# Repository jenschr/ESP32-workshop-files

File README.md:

# ESP32-workshop-files
Kicad files from my two-day workshop at [Bitraf](https://github.com/bitraf) on creating an ESP32 based IoT device from scratch. In the Workshop, attendees will be making an IoT device from scratch using the Open Source EDA software Kicad. [Slides from the workshop](https://www.slideshare.net/jensa/two-day-electronics-workshop-with-kicad-training) can be found at my Slideshare account.

## Reference designs
In the workshop, we'll create our own boards from scratch, but we found that it's convenient to have a project to compare and check things against. In the workshop, the attendees can choose to use either the ESP32 S2/S3 Mini or the ESP32 Wroom 32E modules. The latter requires the use of a serial chip such as the CP2102/04 and this tested design has the required auto-program circuitry.

## Alternate parts
Having a devboard is fun, but having some builtin input and output is even better, so for the attendees that don't have a plan, I've suggested to add an APA102 Dotstar pixel as well as a simple NTC-based temperature sensor. The circuit for these two are in the files for the S2/S3 Mini.

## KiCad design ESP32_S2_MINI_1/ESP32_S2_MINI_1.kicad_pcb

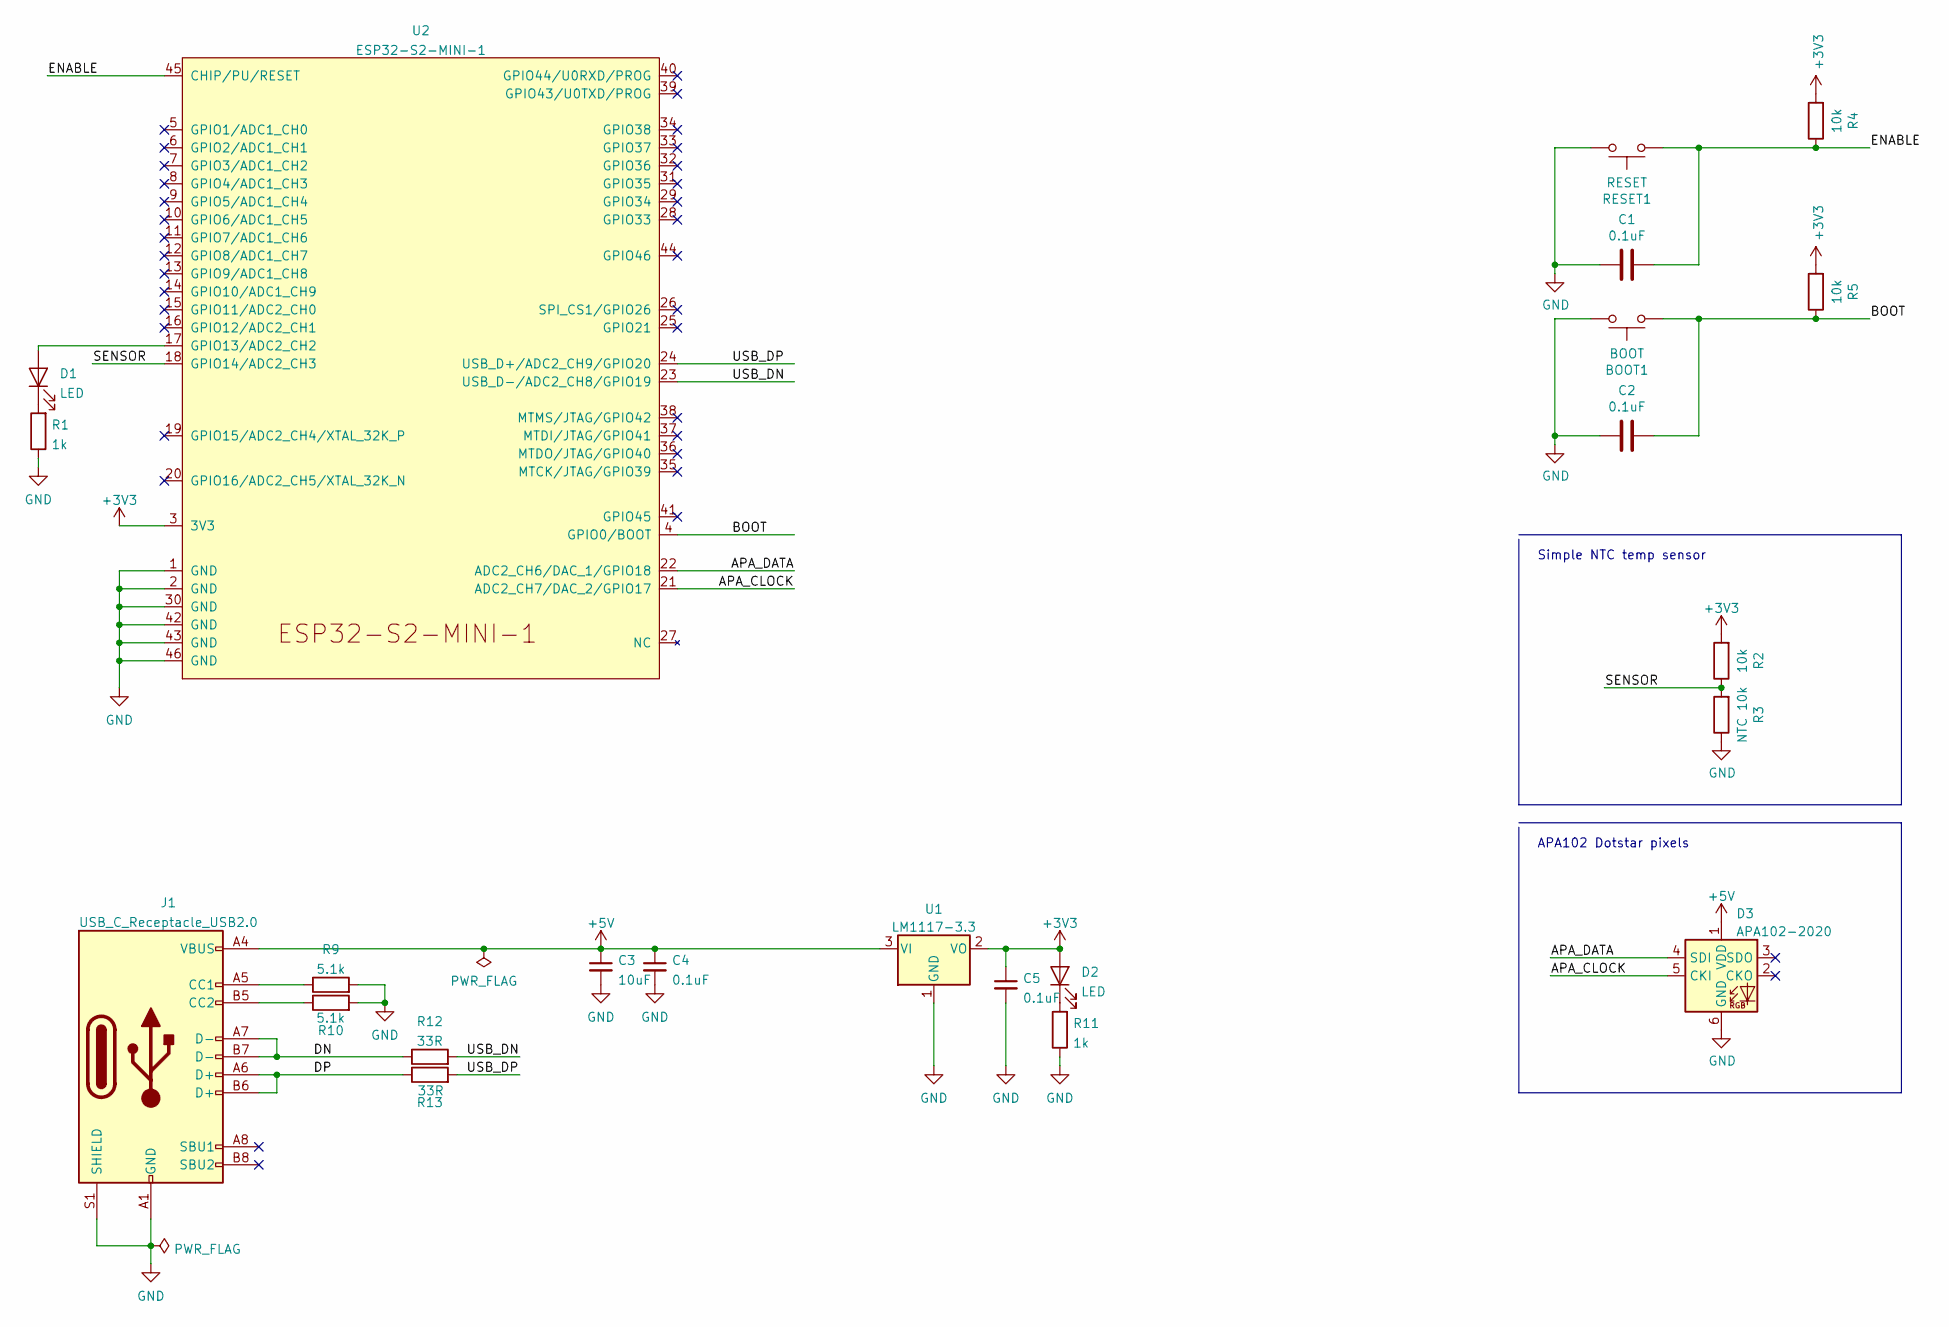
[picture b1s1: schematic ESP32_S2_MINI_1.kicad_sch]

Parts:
BOOT1: BOOT; SW_Push_1P1T_NO_CK_KMR2; MPN KMR241GLFS
C1, C2: 0.1uF; C_0402_1005Metric; MPN CL10B104KO8NFNC
C3: 10uF; C_0603_1608Metric
C4, C5: 0.1uF; C_0402_1005Metric
D1, D2: LED; LED_0402_1005Metric
D3: APA102-2020; LED-APA102-2020
J1: USB_C_Receptacle_USB2.0; TYPE-C-31-M-14
R1, R11: 1k; R_0402_1005Metric
R2, R4, R5: 10k; R_0402_1005Metric; MPN RMCF0603JG10K0
R3: NTC 10k; R_0402_1005Metric; MPN RMCF0603JG10K0
R9, R10: 5.1k; R_0402_1005Metric
R12, R13: 33R; R_0402_1005Metric
RESET1: RESET; SW_Push_1P1T_NO_CK_KMR2; MPN KMR241GLFS
U1: LM1117-3.3; SOT-223
U2: ESP32-S2-MINI-1

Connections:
+3V3: C5.1, D2.2 (A), R2.2, R4.2, R5.2, U1.2 (VO), U2.3 (3V3)
+5V: C3.1, C4.1, D3.1 (VDD), J1.A4 (VBUS), J1.A9 (VBUS), J1.B4 (VBUS), J1.B9 (VBUS), U1.3 (VI)
/APA_CLOCK: D3.5 (CKI), U2.21 (ADC2_CH7/DAC_2/GPIO17)
/APA_DATA: D3.4 (SDI), U2.22 (ADC2_CH6/DAC_1/GPIO18)
/BOOT: BOOT1.1, C2.1, R5.1, U2.4 (GPIO0/BOOT)
/DN: J1.A7 (D-), J1.B7 (D-), R12.1
/DP: J1.A6 (D+), J1.B6 (D+), R13.1
/ENABLE: C1.1, R4.1, RESET1.1, U2.45 (CHIP/PU/RESET)
/SENSOR: R2.1, R3.2, U2.18 (GPIO14/ADC2_CH3)
/USB_DN: R12.2, U2.23 (USB_D-/ADC2_CH8/GPIO19)
/USB_DP: R13.2, U2.24 (USB_D+/ADC2_CH9/GPIO20)
GND: BOOT1.2, C1.2, C2.2, C3.2, C4.2, C5.2, D3.6 (GND), J1.A1 (GND), J1.A12 (GND), J1.B1 (GND), J1.B12 (GND), J1.S1 (SHIELD), R1.1, R3.1, R9.2, R10.2, R11.1, RESET1.2, U1.1 (GND), U2.1 (GND), U2.2 (GND), U2.30 (GND), U2.42 (GND), U2.43 (GND), U2.46 (GND)
unnamed: D1.1 (K), R1.2
unnamed: D1.2 (A), U2.17 (GPIO13/ADC2_CH2)
unnamed: D2.1 (K), R11.2
unnamed: J1.A5 (CC1), R9.1
unnamed: J1.B5 (CC2), R10.1

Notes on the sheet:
Simple NTC temp sensor
APA102 Dotstar pixels

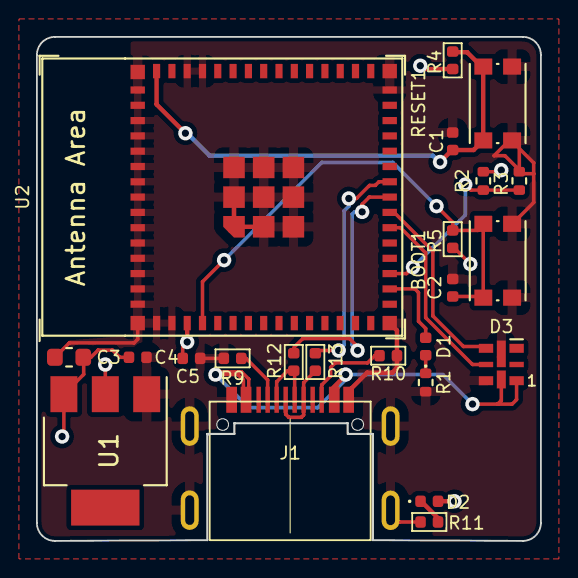
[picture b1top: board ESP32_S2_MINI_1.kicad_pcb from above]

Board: 2 copper layers, 28.0 x 28.0 mm, 23 parts (0 on the bottom side), 17 nets.

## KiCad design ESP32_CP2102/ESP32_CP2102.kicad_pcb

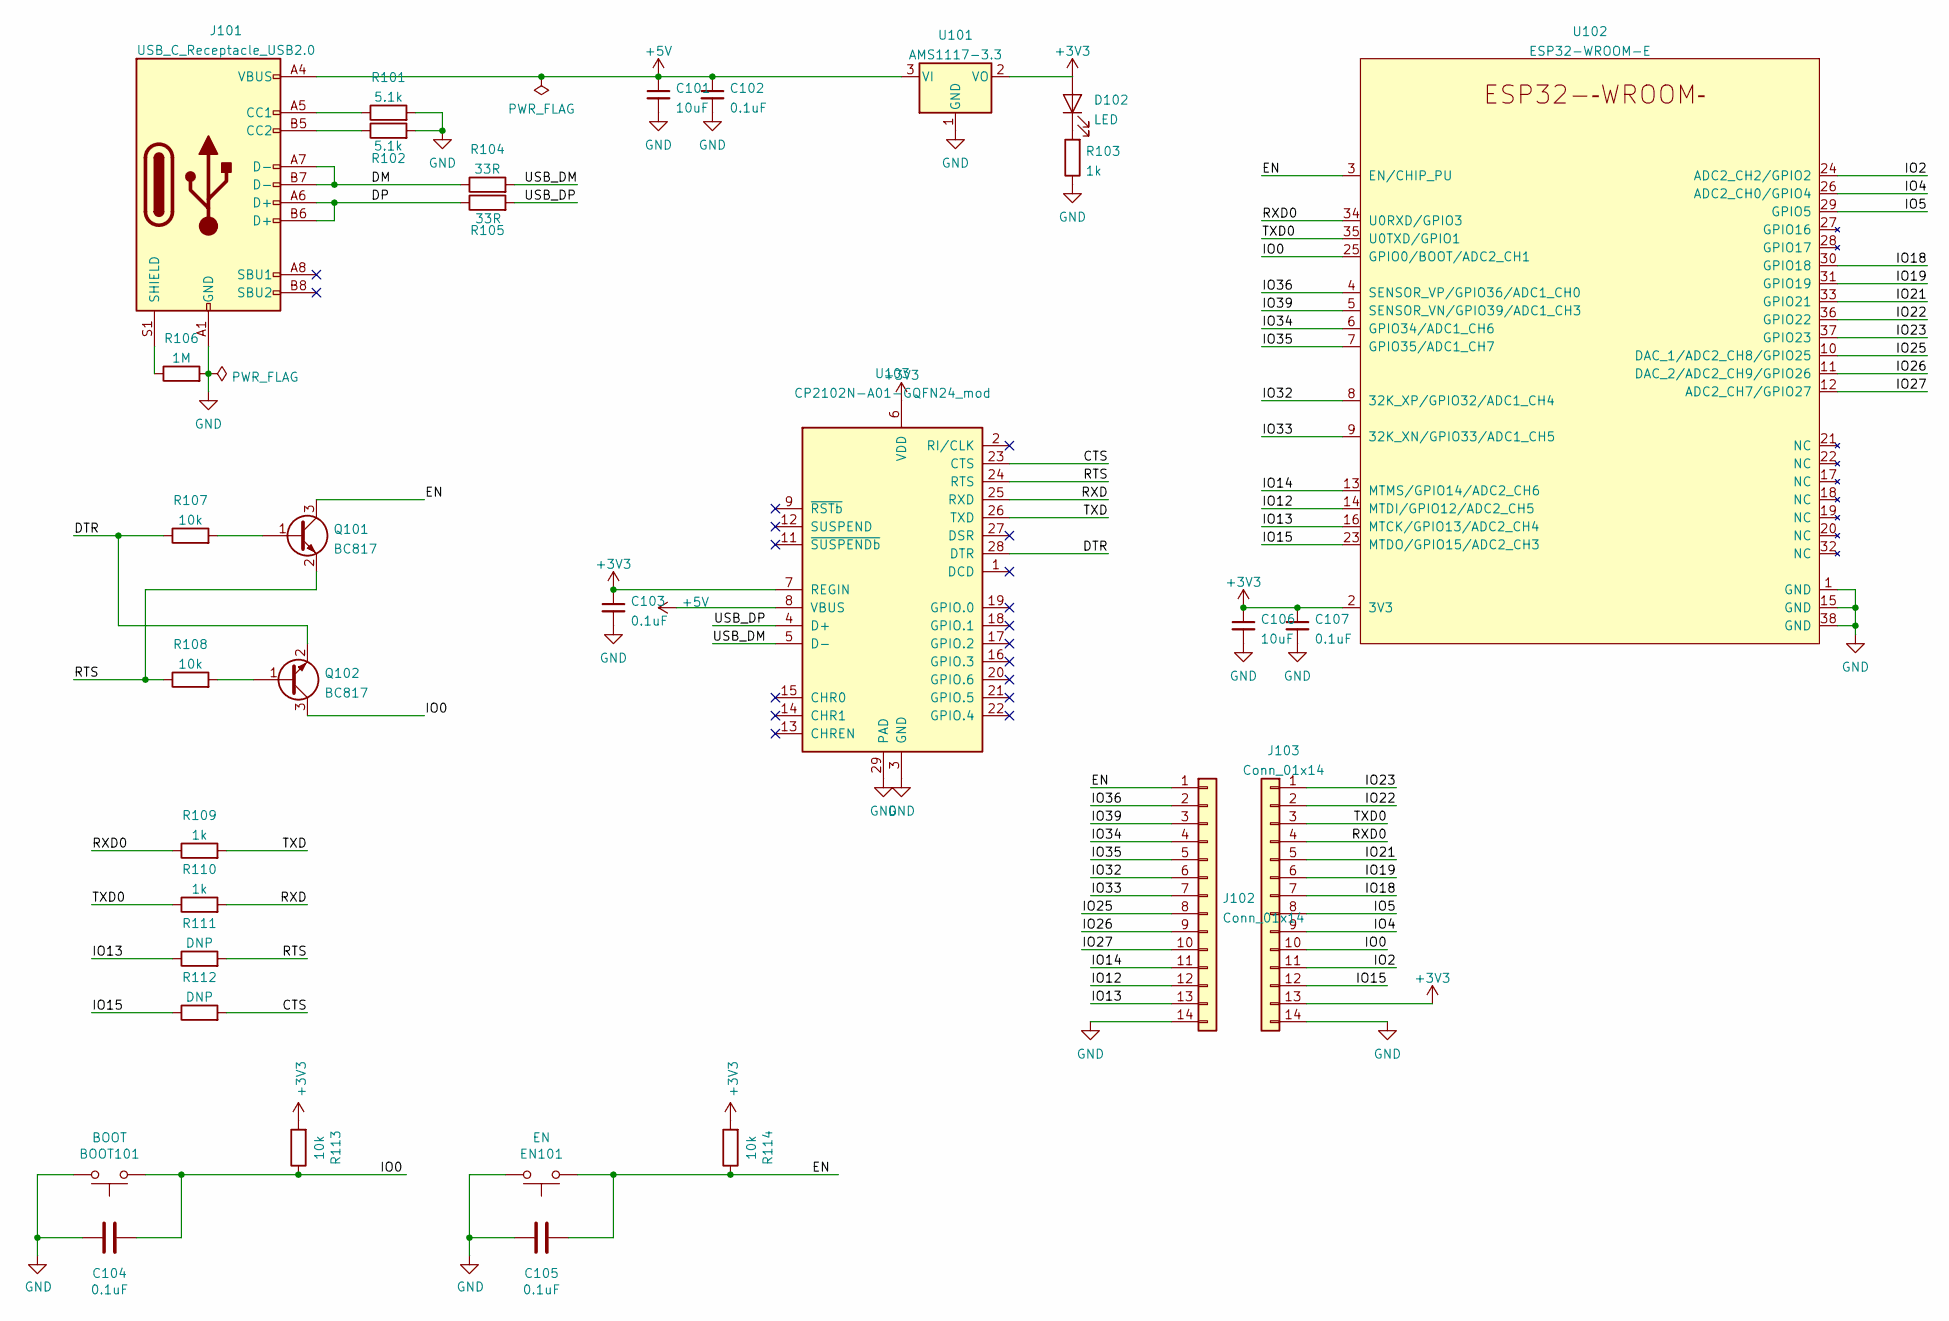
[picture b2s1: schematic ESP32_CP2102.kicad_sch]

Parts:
BOOT101: BOOT; KMR241GLFS; MPN KMR241GLFS
C101, C106: 10uF; C_0805_2012Metric
C102, C103, C107: 0.1uF; C_0603_1608Metric
C104, C105: 0.1uF; C_0603_1608Metric; MPN CL10B104KO8NFNC
D102: LED; LED_0603_1608Metric
EN101: EN; KMR241GLFS; MPN KMR241GLFS
J101: USB_C_Receptacle_USB2.0; TYPE-C-31-M-12
J102, J103: Conn_01x14; PinSocket_1x14_P2.54mm_Vertical
Q101, Q102: BC817; SOT-23
R101, R102: 5.1k; R_0603_1608Metric
R103, R109, R110: 1k; R_0603_1608Metric
R104, R105: 33R; R_0603_1608Metric
R106: 1M; R_0603_1608Metric
R107, R108: 10k; R_0603_1608Metric
R111, R112: DNP; R_0603_1608Metric
R113, R114: 10k; R_0603_1608Metric_Pad1.05x0.95mm_HandSolder; MPN RMCF0603JG10K0
U101: AMS1117-3.3; SOT-223-3_TabPin2
U102: ESP32-WROOM-E; ESP32-WROOM-32E
U103: CP2102N-A01-GQFN24_mod; QFN-28-1EP_5x5mm_P0.5mm_EP3.35x3.35mm

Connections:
+3V3: C103.1, C106.1, C107.1, D102.2 (A), J103.13, R113.2, R114.2, U101.2 (VO), U102.2 (3V3), U103.6 (VDD), U103.7 (REGIN)
+5V: C101.1, C102.1, J101.A4 (VBUS), J101.A9 (VBUS), J101.B4 (VBUS), J101.B9 (VBUS), U101.3 (VI), U103.8 (VBUS)
/CTS: R112.2, U103.23 (CTS)
/DM: J101.A7 (D-), J101.B7 (D-), R104.1
/DP: J101.A6 (D+), J101.B6 (D+), R105.1
/DTR: Q102.2 (E), R107.1, U103.28 (DTR)
/EN: C105.1, EN101.1, J102.1, Q101.3 (C), R114.1, U102.3 (EN/CHIP_PU)
/IO0: BOOT101.1, C104.1, J103.10, Q102.3 (C), R113.1, U102.25 (GPIO0/BOOT/ADC2_CH1)
/IO2: J103.11, U102.24 (ADC2_CH2/GPIO2)
/IO4: J103.9, U102.26 (ADC2_CH0/GPIO4)
/IO5: J103.8, U102.29 (GPIO5)
/IO12: J102.12, U102.14 (MTDI/GPIO12/ADC2_CH5)
/IO13: J102.13, R111.1, U102.16 (MTCK/GPIO13/ADC2_CH4)
/IO14: J102.11, U102.13 (MTMS/GPIO14/ADC2_CH6)
/IO15: J103.12, R112.1, U102.23 (MTDO/GPIO15/ADC2_CH3)
/IO18: J103.7, U102.30 (GPIO18)
/IO19: J103.6, U102.31 (GPIO19)
/IO21: J103.5, U102.33 (GPIO21)
/IO22: J103.2, U102.36 (GPIO22)
/IO23: J103.1, U102.37 (GPIO23)
/IO25: J102.8, U102.10 (DAC_1/ADC2_CH8/GPIO25)
/IO26: J102.9, U102.11 (DAC_2/ADC2_CH9/GPIO26)
/IO27: J102.10, U102.12 (ADC2_CH7/GPIO27)
/IO32: J102.6, U102.8 (32K_XP/GPIO32/ADC1_CH4)
/IO33: J102.7, U102.9 (32K_XN/GPIO33/ADC1_CH5)
/IO34: J102.4, U102.6 (GPIO34/ADC1_CH6)
/IO35: J102.5, U102.7 (GPIO35/ADC1_CH7)
/IO36: J102.2, U102.4 (SENSOR_VP/GPIO36/ADC1_CH0)
/IO39: J102.3, U102.5 (SENSOR_VN/GPIO39/ADC1_CH3)
/RTS: Q101.2 (E), R108.1, R111.2, U103.24 (RTS)
/RXD: R110.2, U103.25 (RXD)
/RXD0: J103.4, R109.1, U102.34 (U0RXD/GPIO3)
/TXD: R109.2, U103.26 (TXD)
/TXD0: J103.3, R110.1, U102.35 (U0TXD/GPIO1)
/USB_DM: R104.2, U103.5 (D-)
/USB_DP: R105.2, U103.4 (D+)
GND: BOOT101.2, C101.2, C102.2, C103.2, C104.2, C105.2, C106.2, C107.2, EN101.2, J101.A1 (GND), J101.A12 (GND), J101.B1 (GND), J101.B12 (GND), J102.14, J103.14, R101.2, R102.2, R103.1, R106.2, U101.1 (GND), U102.1 (GND), U102.15 (GND), U102.38 (GND), U103.3 (GND), U103.29 (PAD)
unnamed: D102.1 (K), R103.2
unnamed: J101.A5 (CC1), R101.1
unnamed: J101.B5 (CC2), R102.1
unnamed: J101.S1 (SHIELD), R106.1
unnamed: Q101.1 (B), R107.2
unnamed: Q102.1 (B), R108.2

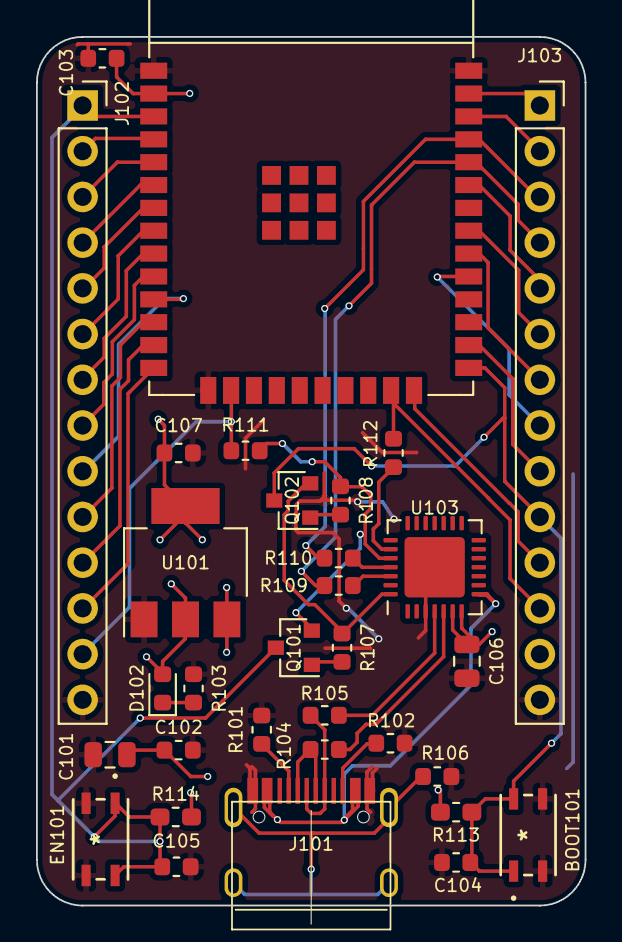
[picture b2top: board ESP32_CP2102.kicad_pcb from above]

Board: 2 copper layers, 30.5 x 48.3 mm, 32 parts (0 on the bottom side), 43 nets.

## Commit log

2022-03-24 Kicad examples and notes added

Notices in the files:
parts and their libraries:
Copyright 2016 Accelerated Designs. All rights reserved.
